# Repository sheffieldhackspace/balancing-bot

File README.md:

The **inkscapeFiles** directory contains all the files and instructions needed to laser cut a frame for the self-balancing bot.

All the files needed for the pcb (including gerber files) are located in **kicadFiles**.

Remember to solder the HC-05 bluetooth module on last!
The R1 resistor value should be 2K ohms, whilst for R2 it's 1k ohms.

The Arduino code is a modified version of that developed by [http://www.klikrobotics.com](http://www.klikrobotics.com) and was downloaded from their repository at [https://github.com/garethnisbet/T-BOTS](https://github.com/garethnisbet/T-BOTS). The code was branched off in Oct 2018 and is therefore out of date but it works!

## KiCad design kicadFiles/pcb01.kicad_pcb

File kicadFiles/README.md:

Drag and drop the /gerber files to 

[https://www.pcbgogo.com/GerberViewer.html](https://www.pcbgogo.com/GerberViewer.html)

to view the pcb in 2D, or to

[http://mayhewlabs.com/webGerber](http://mayhewlabs.com/webGerber)

to view them in 3D.

If you want to order some pcbs from somewhere then usually you need to .zip these files and then upload them.  
#

The pcb designs were created using KiCad v5.0. If you want to modify the design and create your own gerber files then you need to do the following:

1. Open pcb01.kicad_pcb with pcbnew
2. Go to File -> File Plot
3. Press the 'Plot' button and then press the 'Generate Drill Files' button
4. Select 'Zeros Format:Keep zeros' and then press the 'Generate Drill File' button.

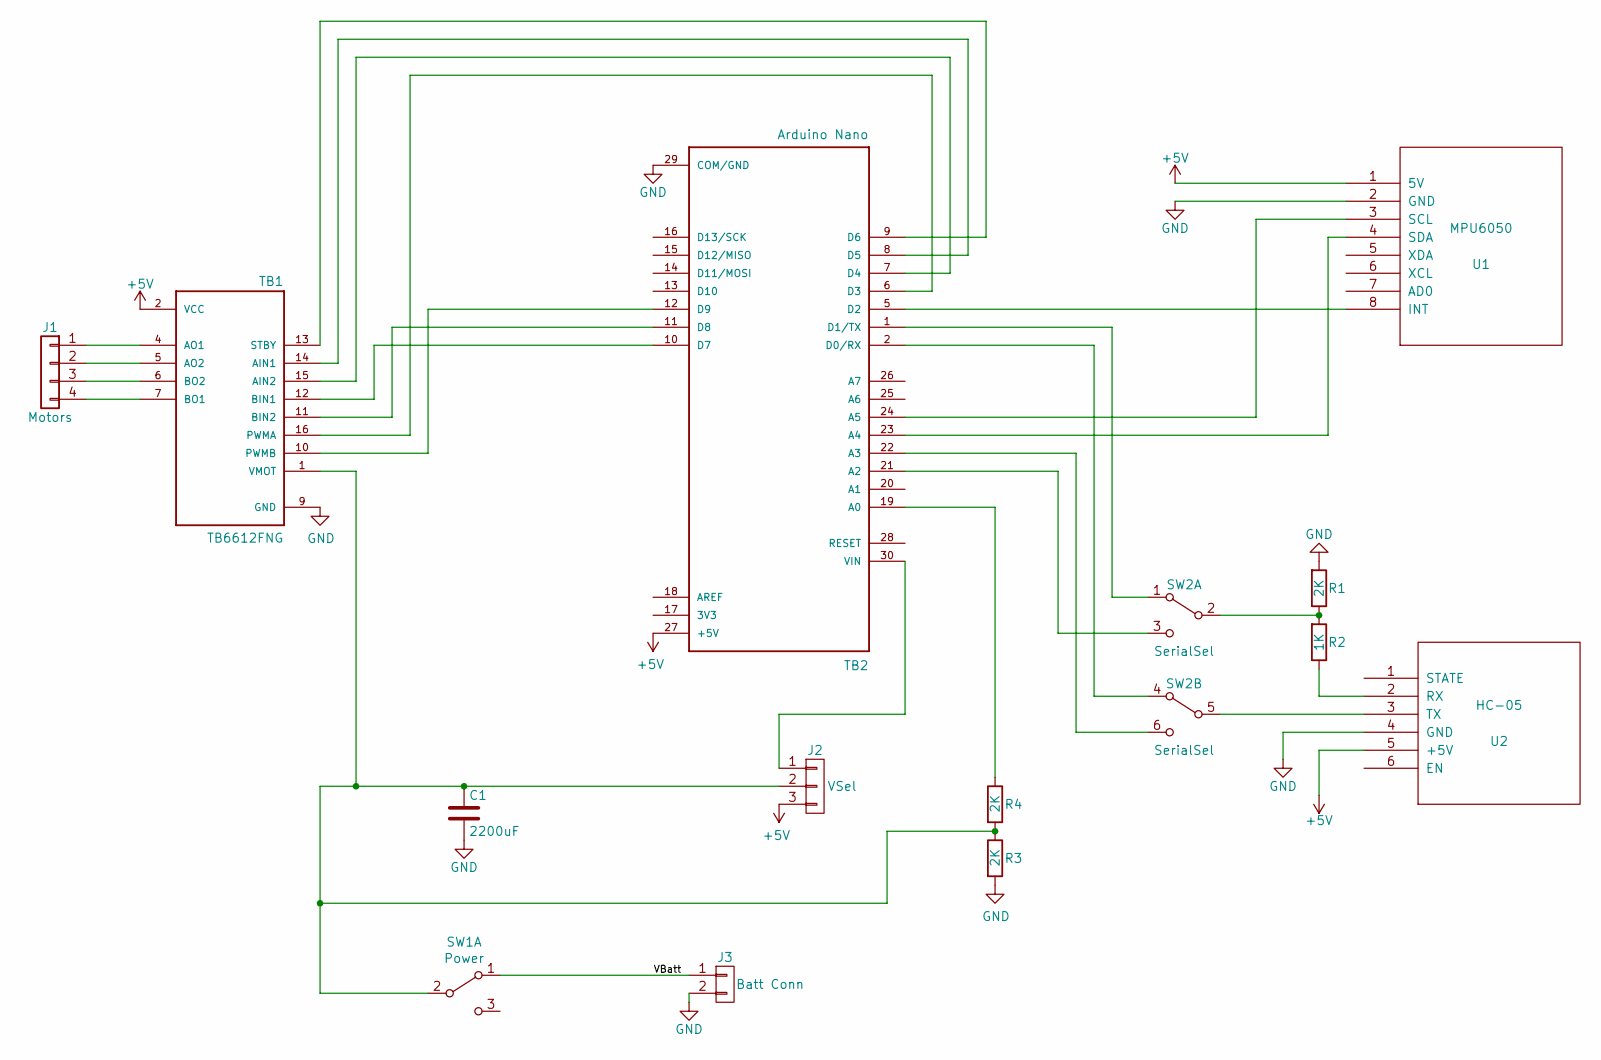
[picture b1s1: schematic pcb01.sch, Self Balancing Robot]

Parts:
C1: 2200uF; C_Radial_D10.0mm_H20.0mm_P5.00mm
J1: Motors; PinHeader_1x04_P2.54mm_Vertical
J2: VSel; PinHeader_1x03_P2.54mm_Vertical
J3: Batt Conn; PinHeader_1x02_P2.54mm_Vertical
R1, R3, R4: 2K; R_Axial_DIN0207_L6.3mm_D2.5mm_P10.16mm_Horizontal
R2: 1K; R_Axial_DIN0207_L6.3mm_D2.5mm_P10.16mm_Horizontal
SW1: Power; SW_CuK_JS202011CQN_DPDT_Straight
SW2: SerialSel; SW_CuK_JS202011CQN_DPDT_Straight
TB1: TB6612FNG; Pololu_Breakout-16_15.2x20.3mm
TB2: Arduino Nano; Arduino_Nano
U1: MPU6050; PinHeader_1x08_P2.54mm_Vertical
U2: HC-05; PinHeader_1x06_P2.54mm_Vertical

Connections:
+5V: J2.3, TB1.2 (VCC), TB2.27 (+5V), U1.1 (5V), U2.5 (+5V)
/VBatt: J3.1, SW1.1 (A)
COM/GND: C1.2, J3.2, R1.2, R3.2, TB1.3 (GND), TB1.8 (GND), TB1.9 (GND), TB2.4 (COM/GND), TB2.29 (COM/GND), U1.2 (GND), U2.4 (GND)
unnamed: C1.1, J2.2, R3.1, R4.2, SW1.2 (B), TB1.1 (VMOT)
unnamed: J1.1, TB1.4 (AO1)
unnamed: J1.2, TB1.5 (AO2)
unnamed: J1.3, TB1.6 (BO2)
unnamed: J1.4, TB1.7 (BO1)
unnamed: J2.1, TB2.30 (VIN)
unnamed: R1.1, R2.2, SW2.2 (B)
unnamed: R2.1, U2.2 (RX)
unnamed: R4.1, TB2.19 (A0)
unnamed: SW2.1 (A), TB2.1 (D1/TX)
unnamed: SW2.3 (C), TB2.21 (A2)
unnamed: SW2.4 (A), TB2.2 (D0/RX)
unnamed: SW2.5 (B), U2.3 (TX)
unnamed: SW2.6 (C), TB2.22 (A3)
unnamed: TB1.10 (PWMB), TB2.12 (D9)
unnamed: TB1.11 (BIN2), TB2.11 (D8)
unnamed: TB1.12 (BIN1), TB2.10 (D7)
unnamed: TB1.13 (STBY), TB2.9 (D6)
unnamed: TB1.14 (AIN1), TB2.8 (D5)
unnamed: TB1.15 (AIN2), TB2.7 (D4)
unnamed: TB1.16 (PWMA), TB2.6 (D3)
unnamed: TB2.5 (D2), U1.8 (INT)
unnamed: TB2.23 (A4), U1.4 (SDA)
unnamed: TB2.24 (A5), U1.3 (SCL)

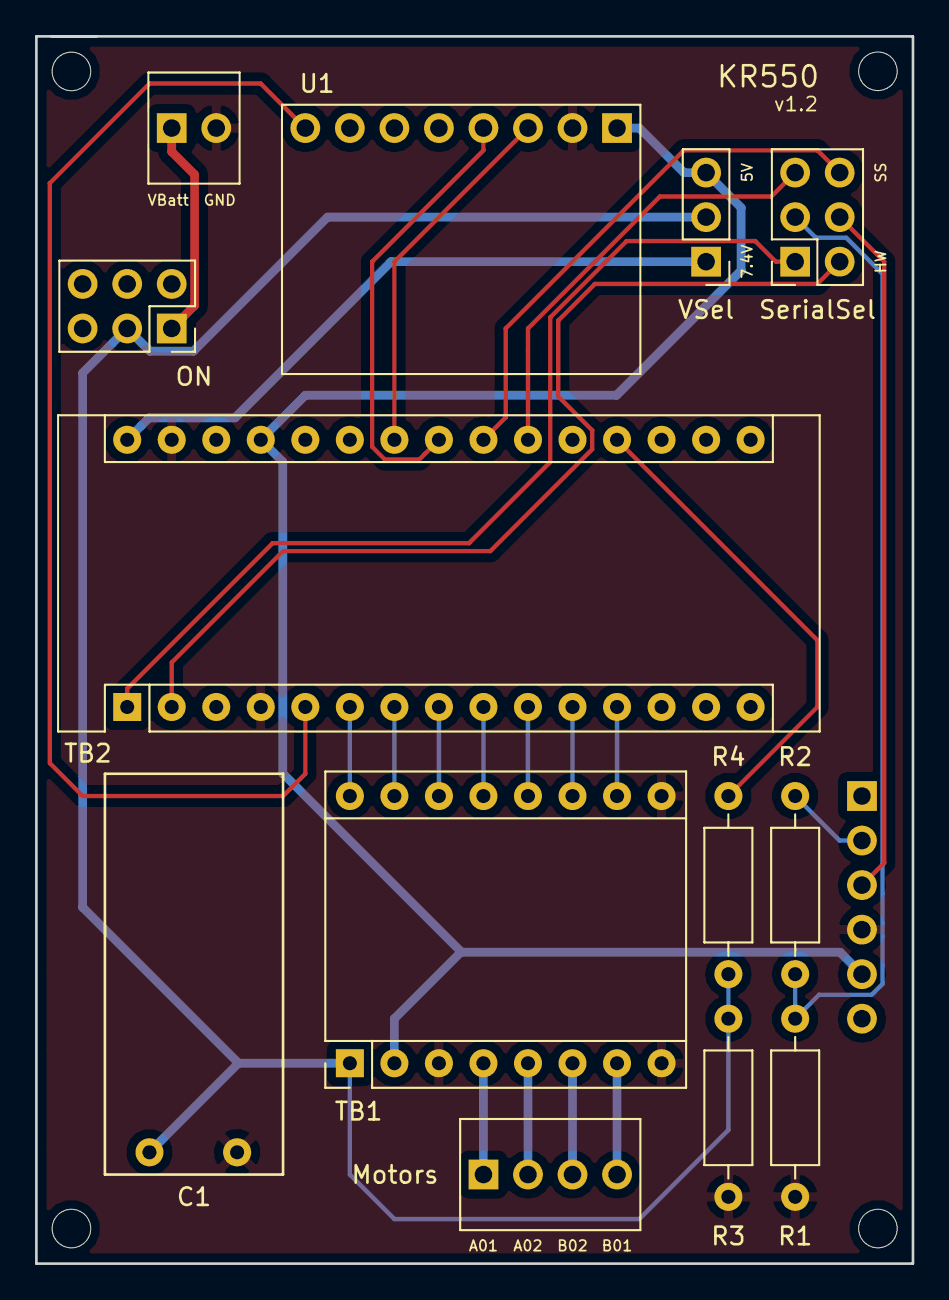
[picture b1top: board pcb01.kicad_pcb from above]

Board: 2 copper layers, 50.0 x 70.0 mm, 14 parts (1 on the bottom side), 27 nets.

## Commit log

2019-05-14 Create LICENSE
2019-05-18 added test file
2019-05-23 Rename README.md to inkscapeFiles/README.md
2019-05-23 Rename frame.3xAA.svg to inkscapeFiles/frame.3xAA.svg
2019-05-23 Rename frame.li-ion.svg to inkscapeFiles/frame.li-ion.svg
2019-05-26 Rename Arduino/BluetoothChangeName/BluetoothChangeName.ino to Arduino/changebaudrate/changebaudrate.ino
